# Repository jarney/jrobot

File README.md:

# JRobot Introduction

This project aims to make available a high quality, low cost robot arm for the home hobbyist.

## Quality
* Repeatable: gear mechanisms with small backlash and repeatable moves.
* Safe: Limit switches all around to ensure within tolerances.
* Callibration: Custom callibration cycle similar to Prusa mesh leveling procedure to ensure repeatable moves and measured tolerances.
* Feedback: Closed-loop encoders where possible (but not required)
* Reliable: Be aware of vibration-sensitive connections and try to reduce the vibrarion or otherwise prevent loosening during operation.

## [Getting parts](bill-of-materials/README.md)

There is a bill of materials for the build.  The parts are a combination of commonly available bolts, bearings, motors, and switches as well as 
3d-printed and other custom parts.

## [Build Guide](build-guide/README.md)
The assembly can be done using the build instructions.  The instructions include written instructions as well as
a number of videos showing the assembly.

## [CAD](freecad/README.md)

The CAD is done using FreeCad.  There is a guide to the [CAD files](FreeCAD/README.md) if you would like to modify the design.

## [3d Printing of parts](3d-printing/README.md)

Some of the parts are 3d-printed.  The STL files are available with a printing guide.

## Design Goals:

This section describes some of the design goals of the project.  This is mainly to keep the team honest
when making design choices and specifically to differentiate from other similar robot arm projects
which have slightly different design goals.

### Inexpensive:

In order to keep the project inexpensive, it is important for the off-the-shelf components
used be commonly available and inexpensive.  In addition, many of the off-the-shelf components
are less expensive per unit when purchased in bulk.  For example, ISO M3 screws are less expensive
in a box of 100 than they are for individual purchase of screws.  From a design perspective, this means
that it is more desirable to have a small variety of fasteners to increase the likihood that they can be
aquired in bulk.

It should also go without saying that less is more.  Reducing the number of bearings and variety
of 'uncommon' or 'large' bearings is important because bearings and other precision parts can sometimes
be expensive.  Also, substituting 3d-printed bearings in some places may be a more accessible option,
especially when the tolerance or wear characteristics of the bearings are not critical.

### Reliability

Continuous operation should be possible for hundreds of hours without a breakdown.  Experience with similar
projects indicates that the two major areas where this can be problematic from a design perspective
are the wiring and vibration.

For wiring, the most common area is cable fatigue from repeated movement.  Good cable management
and isolating the areas of cable motion are critical for improving the reliability.  The design
should ensure that moving cables be kept to a short length and well protected from abrasion.

For vibration, the most common issue is fasteners loosening with nuts falling off.  Wherever possible,
it should be ensured that fasteners can be tightened strongly and where possible, caps added to prevent
nuts from rotating under vibration.  Radial loads on fasteners should also be avoided and
instead, axial loads preferred because this prevents the fasteners from experiencing loads that are
likely to loosen them.

### Fast construction

It is also a design goal to ensure that the project is easy to assemble.  Specificlaly,
special-purpose tools and tight squeezes for inserting fasteners should be avoided.

The only equipment required should be restricted to things commonly available in a home shop.
* 3d Printer (for producing the special-purpose parts).
* Metric hex wrenches
* Soldering iron and crimp tool for building electrical systems.

It may be desirable, if the popularity of the project grows, to custom-build a 
PCB for system control in order to prevent the need to custom solder a breakout board
for the arduino.

### Open-source

The last design goal is for the entire project from CAD to construction be open-source.
This means using tools and techniques that are accessible and open-source with a permissive
license allowing modification at all levels of the project.

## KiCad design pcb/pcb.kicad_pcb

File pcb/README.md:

# PC Board : CNC Shield for 6 axis control

This is a KiCad design for the Arduino Mega shield for robot/CNC
control.  It is designed to plug directly into the
Arduino Mega programmed with the uCNC firmware and
connect via DuPont connectors to the CNC Shield,
limit switches, and servos.

It can be ordered from PCBWay or other PCB
manufacturing shops.

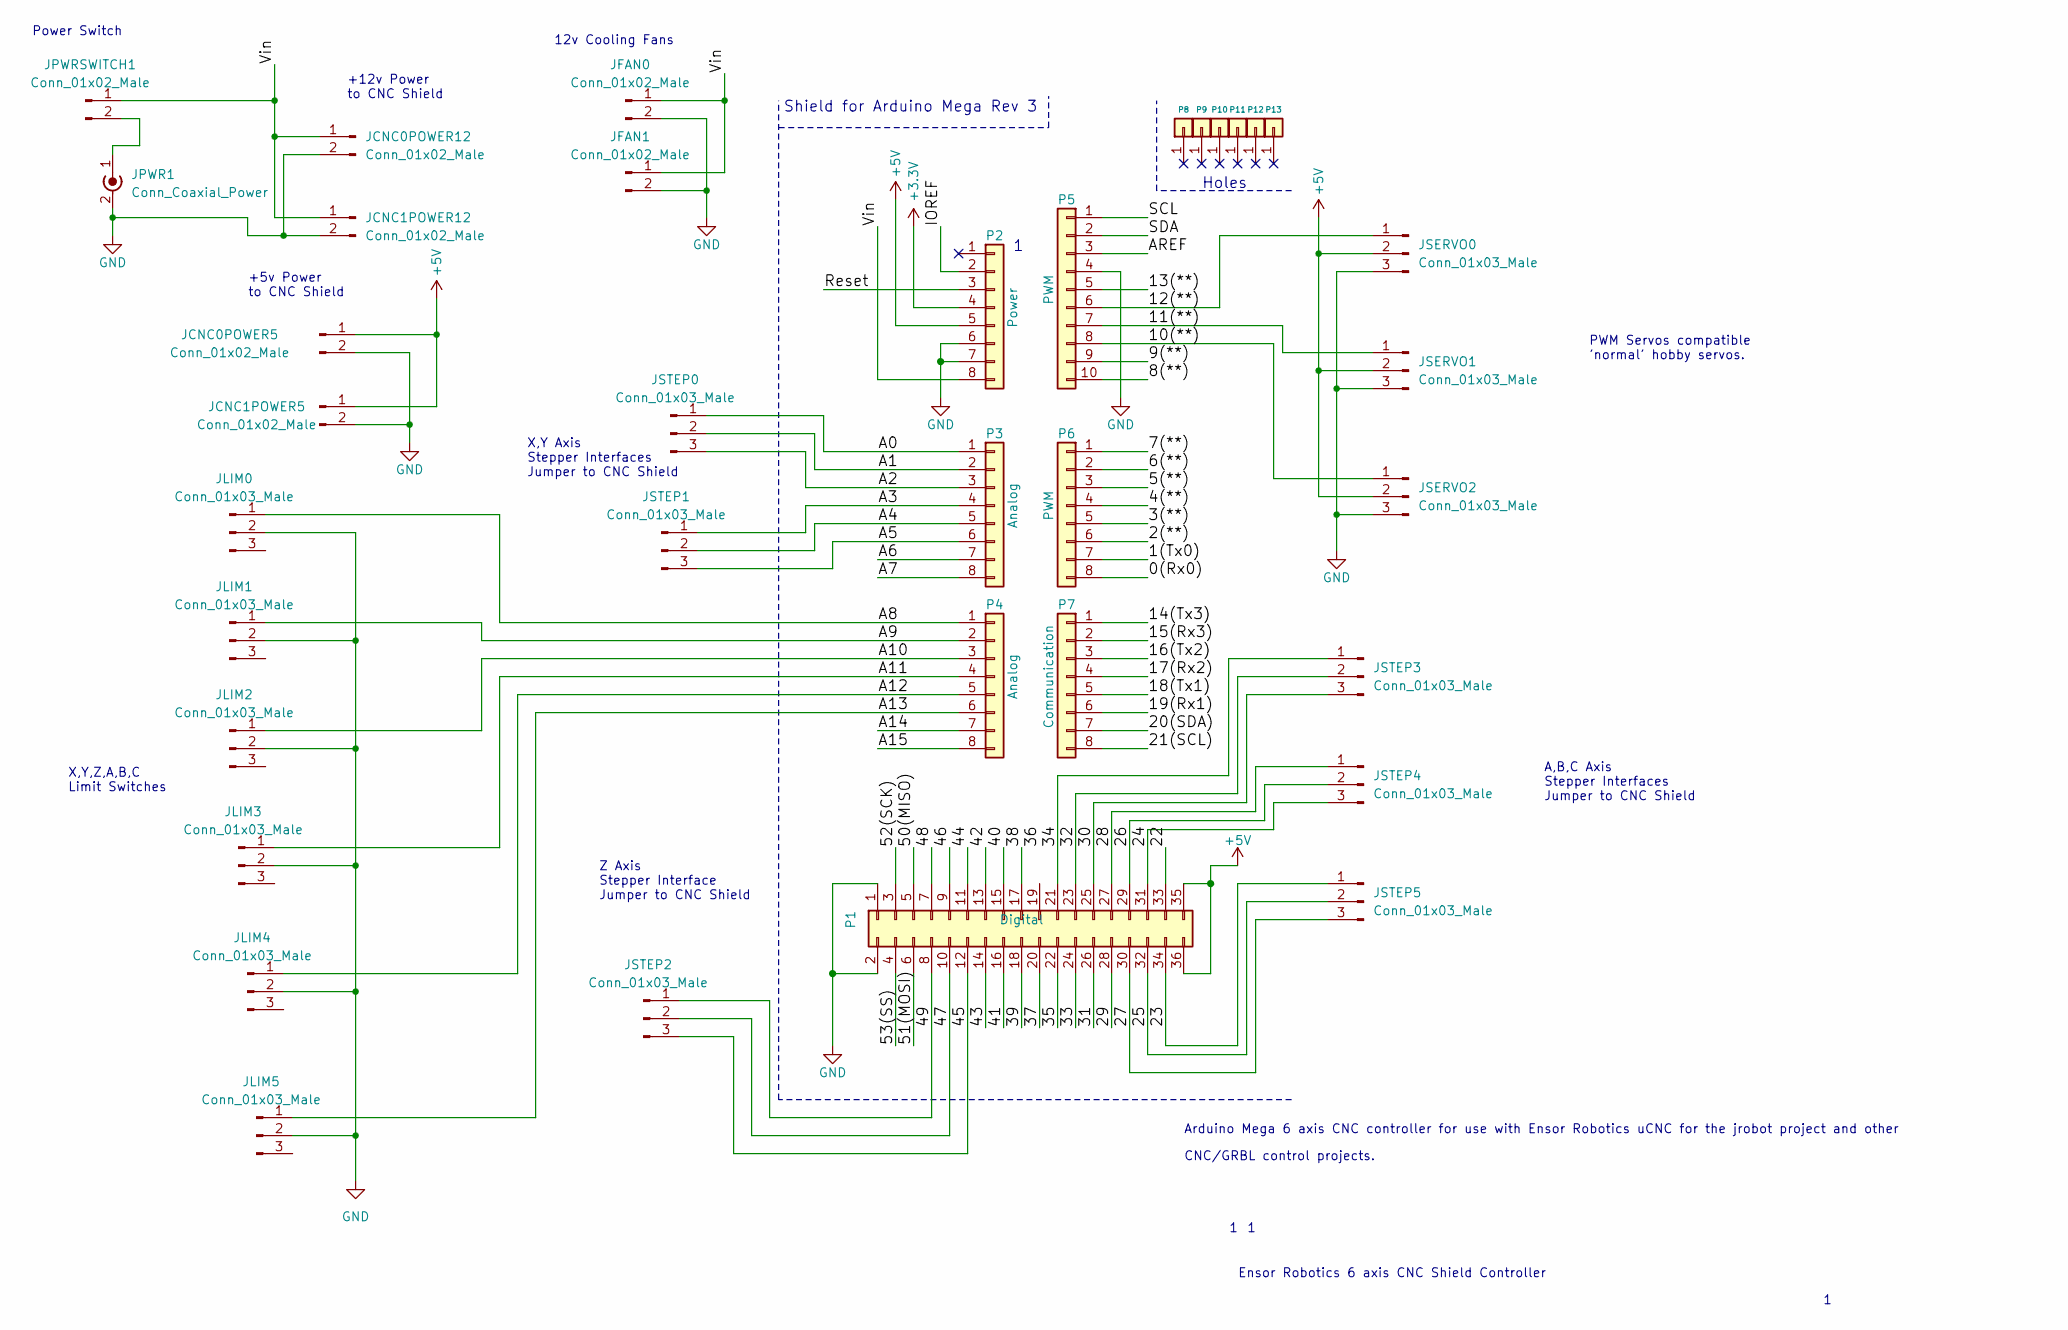
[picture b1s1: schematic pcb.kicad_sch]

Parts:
JCNC0POWER5, JCNC0POWER12, JCNC1POWER5, JCNC1POWER12: Conn_01x02_Male; PinHeader_1x02_P2.54mm_Vertical
JFAN0, JFAN1: Conn_01x02_Male; PinHeader_1x02_P2.54mm_Vertical
JLIM0, JLIM1, JLIM2, JLIM3, JLIM4, JLIM5: Conn_01x03_Male; PinHeader_1x03_P2.54mm_Vertical
JPWR1: Conn_Coaxial_Power; PinHeader_1x02_P2.54mm_Vertical
JPWRSWITCH1: Conn_01x02_Male; PinHeader_1x02_P2.54mm_Vertical
JSERVO0, JSERVO1, JSERVO2: Conn_01x03_Male; PinHeader_1x03_P2.54mm_Vertical
JSTEP0, JSTEP1, JSTEP2, JSTEP3, JSTEP4, JSTEP5: Conn_01x03_Male; PinHeader_1x03_P2.54mm_Vertical
P1: Digital; Socket_Strip_Arduino_2x18
P2: Power; Socket_Strip_Arduino_1x08
P3, P4: Analog; Socket_Strip_Arduino_1x08
P5: PWM; Socket_Strip_Arduino_1x10
P6: PWM; Socket_Strip_Arduino_1x08
P7: Communication; Socket_Strip_Arduino_1x08
P8, P9, P10, P11, P12, P13: CONN_01X01; Arduino_1pin

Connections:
+3V3: P2.4
+5V: JCNC0POWER5.1, JCNC1POWER5.1, JSERVO0.2, JSERVO1.2, JSERVO2.2, P1.35, P1.36, P2.5
/0(Rx0): P6.8
/1(Tx0): P6.7
/2(**): P6.6
/3(**): P6.5
/4(**): P6.4
/5(**): P6.3
/6(**): P6.2
/7(**): P6.1
/8(**): P5.10
/9(**): P5.9
/10(**): JSERVO2.1, P5.8
/11(**): JSERVO1.1, P5.7
/12(**): JSERVO0.1, P5.6
/13(**): P5.5
/14(Tx3): P7.1
/15(Rx3): P7.2
/16(Tx2): P7.3
/17(Rx2): P7.4
/18(Tx1): P7.5
/19(Rx1): P7.6
/20(SDA): P7.7
/21(SCL): P7.8
/22: P1.33
/23: JSTEP5.1, P1.34
/24: JSTEP4.3, P1.31
/25: JSTEP5.2, P1.32
/26: JSTEP4.2, P1.29
/27: JSTEP5.3, P1.30
/28: JSTEP4.1, P1.27
/29: P1.28
/30: JSTEP3.3, P1.25
/31: P1.26
/32: JSTEP3.2, P1.23
/33: P1.24
/34: JSTEP3.1, P1.21
/35: P1.22
/37: P1.20
/38: P1.17
/39: P1.18
/40: P1.15
/41: P1.16
/42: P1.13
/43: P1.14
/44: P1.11
/45: JSTEP2.3, P1.12
/46: P1.9
/47: JSTEP2.2, P1.10
/48: P1.7
/49: JSTEP2.1, P1.8
/50(MISO): P1.5
/51(MOSI): P1.6
/52(SCK): P1.3
/53(SS): P1.4
/A0: JSTEP0.1, P3.1
/A1: JSTEP0.2, P3.2
/A2: JSTEP0.3, P3.3
/A3: JSTEP1.1, P3.4
/A4: JSTEP1.2, P3.5
/A5: JSTEP1.3, P3.6
/A6: P3.7
/A7: P3.8
/A8: JLIM0.1, P4.1
/A9: JLIM1.1, P4.2
/A10: JLIM2.1, P4.3
/A11: JLIM3.1, P4.4
/A12: JLIM4.1, P4.5
/A13: JLIM5.1, P4.6
/A14: P4.7
/A15: P4.8
/AREF: P5.3
/IOREF: P2.2
/Reset: P2.3
/SCL: P5.1
/SDA: P5.2
/Vin: JCNC0POWER12.1, JCNC1POWER12.1, JFAN0.1, JFAN1.1, JPWRSWITCH1.1, P2.8
GND: JCNC0POWER5.2, JCNC0POWER12.2, JCNC1POWER5.2, JCNC1POWER12.2, JFAN0.2, JFAN1.2, JLIM0.2, JLIM1.2, JLIM2.2, JLIM3.2, JLIM4.2, JLIM5.2, JPWR1.2 (Ext), JSERVO0.3, JSERVO1.3, JSERVO2.3, P1.1, P1.2, P2.6, P2.7, P5.4
unnamed: JPWR1.1 (In), JPWRSWITCH1.2

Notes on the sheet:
Z Axis Stepper Interface Jumper to CNC Shield
12v Cooling Fans
A,B,C Axis Stepper Interfaces Jumper to CNC Shield
X,Y,Z,A,B,C Limit Switches
Power Switch
+5v Power to CNC Shield
X,Y Axis Stepper Interfaces Jumper to CNC Shield
Ensor Robotics 6 axis CNC Shield Controller
Holes
PWM Servos compatible 'normal' hobby servos.
Arduino Mega 6 axis CNC controller for use with Ensor Robotics uCNC for the jrobot project and other
CNC/GRBL control projects.
+12v Power to CNC Shield
Shield for Arduino Mega Rev 3

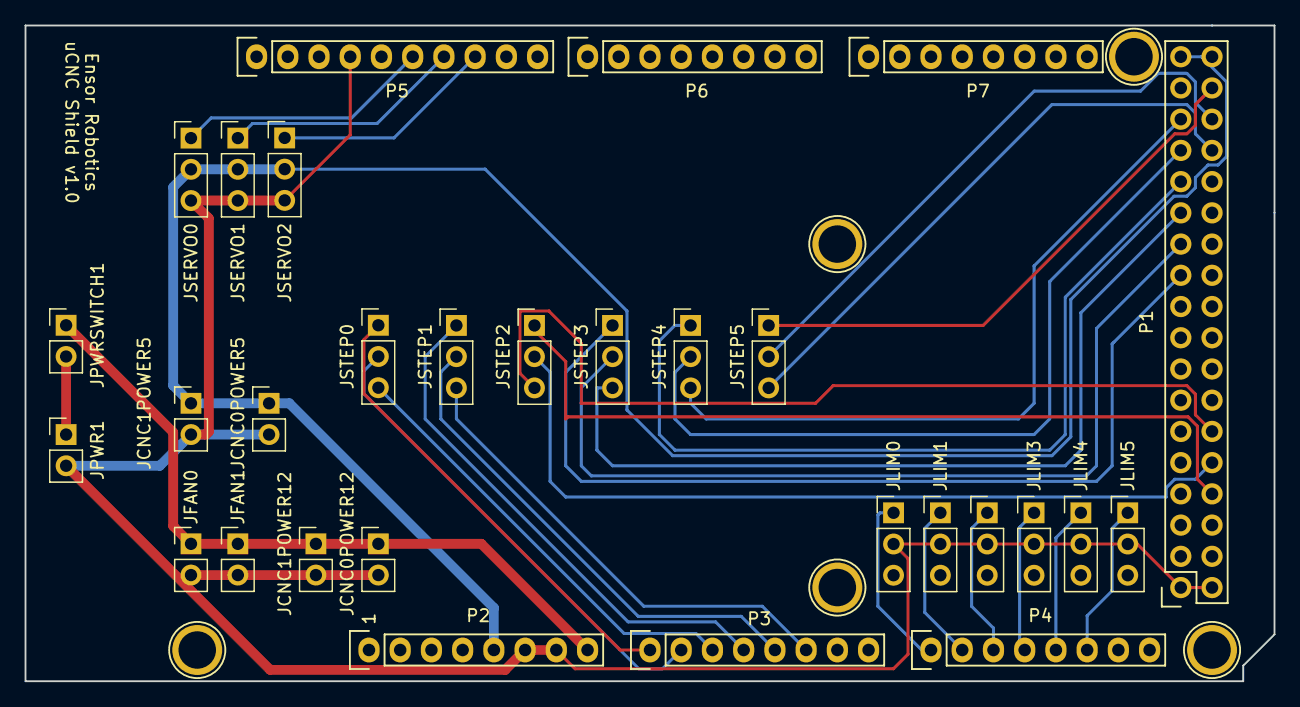
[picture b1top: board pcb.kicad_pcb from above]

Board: 2 copper layers, 101.6 x 53.3 mm, 35 parts (0 on the bottom side), 31 nets.

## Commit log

2024-04-10 Re-started the repository without the un-needed OBJ files to produce animations since those can all be derived from the source CAD files.
2024-04-10 Added PCB drawing to source control for reference in documents.
2024-04-11 Reconciled github project with new changes.
2024-05-20 Added workbench.
2024-05-20 Added STL for workbench templates.
